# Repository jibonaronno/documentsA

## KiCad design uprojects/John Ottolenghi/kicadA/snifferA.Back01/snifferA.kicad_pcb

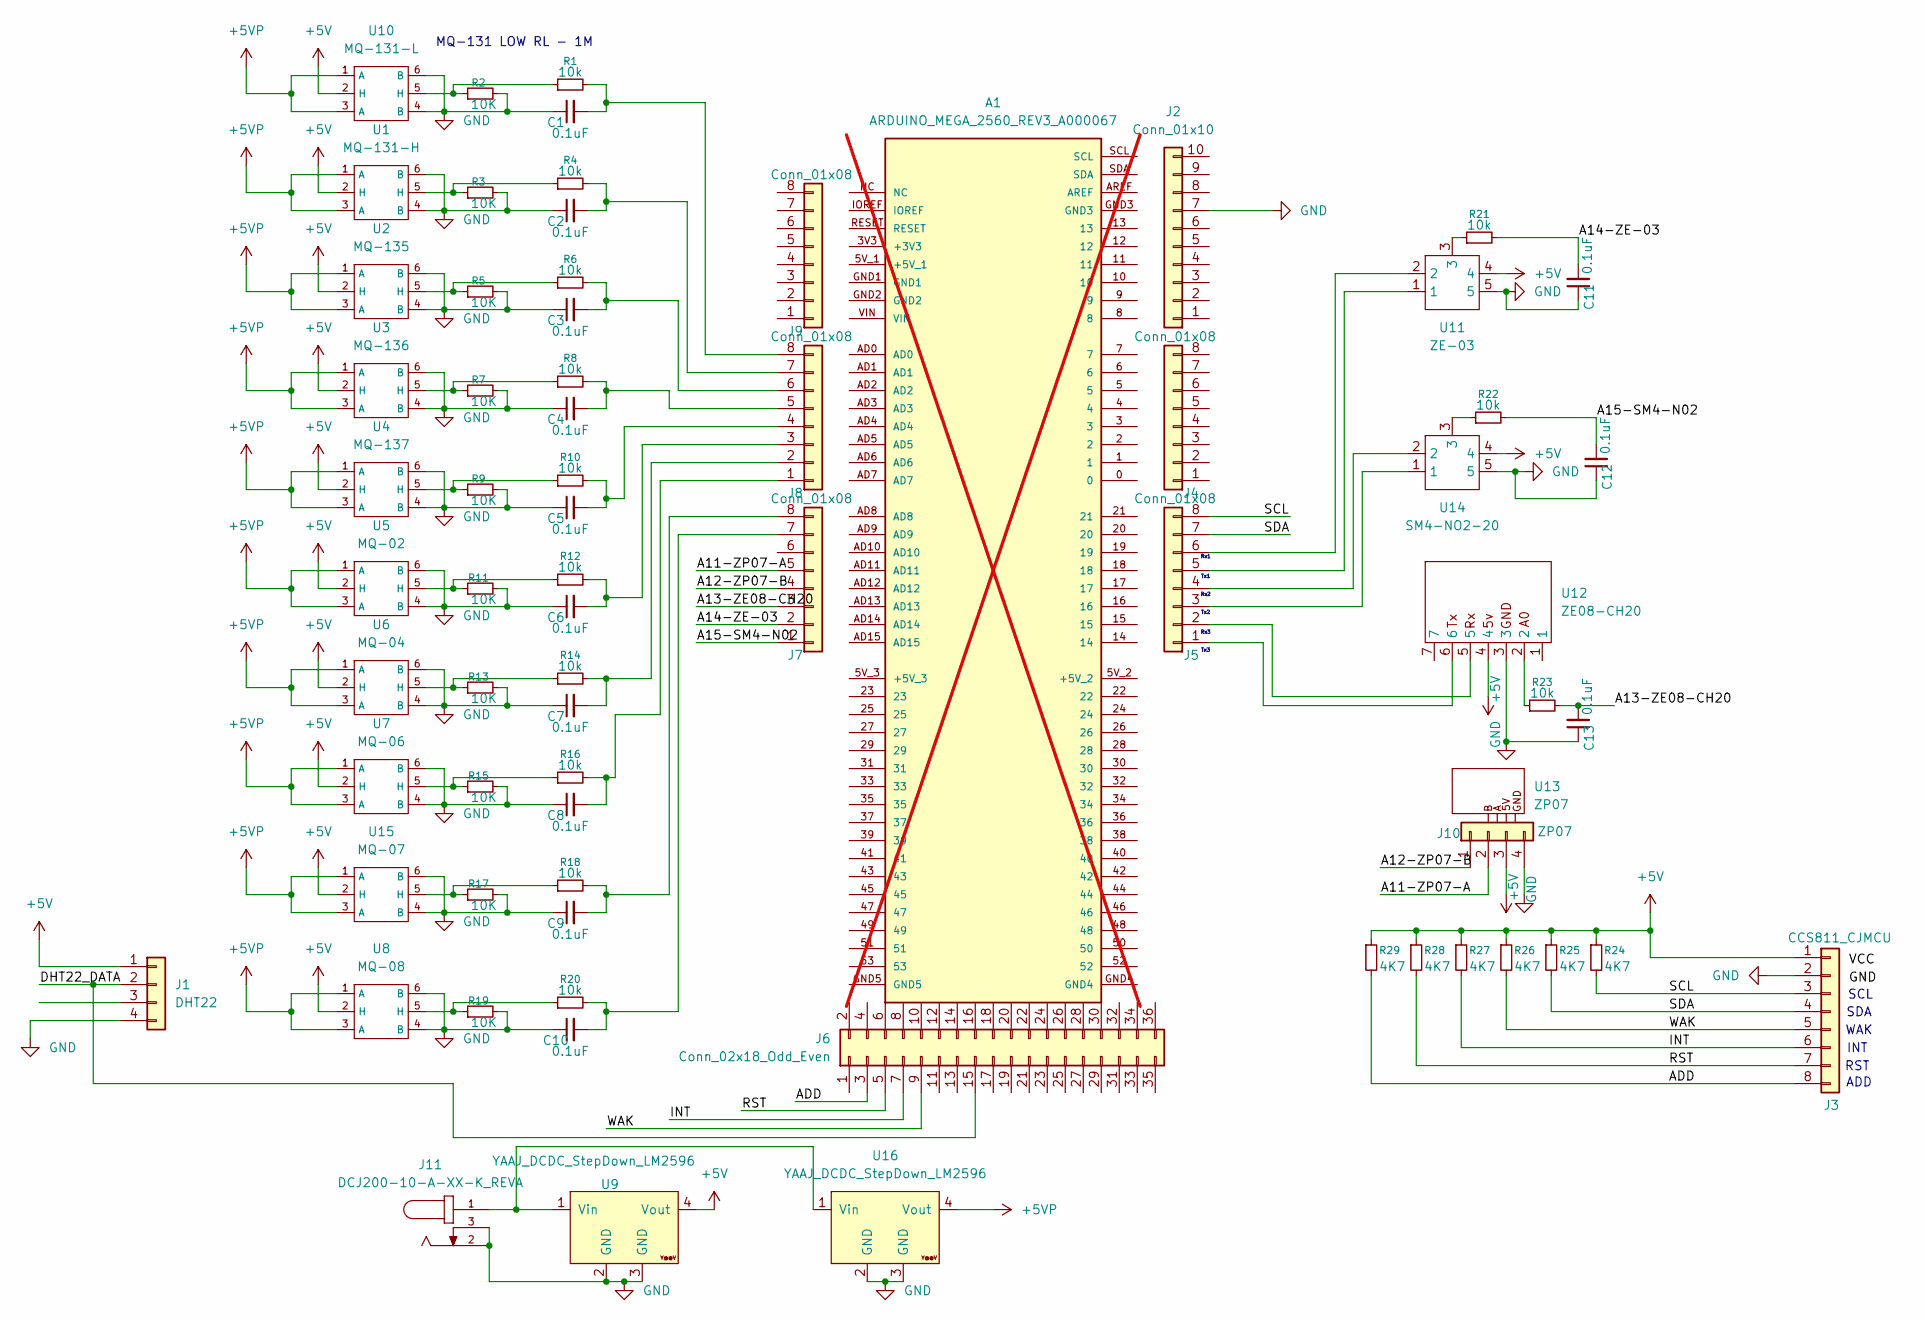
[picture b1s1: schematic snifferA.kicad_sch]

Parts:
A1: ARDUINO_MEGA_2560_REV3_A000067; ARDUINO_ARDUINO_MEGA_2560_REV3_A000067; PARTREV 3; not fitted
C1, C2, C3, C4, C5, C6, C7, C8, C9, C10, C11, C12, C13: 0.1uF; C_1206_3216Metric_Pad1.33x1.80mm_HandSolder; LCSC C24497
J1: DHT22; PinSocket_1x04_P2.54mm_Vertical
J2: Conn_01x10; PinHeader_1x10_P2.54mm_Vertical; LCSC C42431810
J3: CCS811_CJMCU; PinHeader_1x08_P2.54mm_Vertical; LCSC C6332201
J4, J5, J7, J8, J9: Conn_01x08; PinHeader_1x08_P2.54mm_Vertical; LCSC C6332201
J6: Conn_02x18_Odd_Even; PinHeader_2x18_P2.54mm_Vertical; LCSC C41376109
J10: ZP07; PinSocket_1x04_P2.54mm_Vertical
J11: DCJ200-10-A-XX-K_REVA; GCT_DCJ200-10-A-XX-K_REVA; PARTREV A
R1, R4, R6, R8, R10, R12, R14, R16, R18, R20, R21, R22, R23: 10k; R_1206_3216Metric; LCSC C2907370
R2, R3, R5, R7, R9, R11, R13, R15, R17, R19: 10K; R_1206_3216Metric; LCSC C2907370
R24, R25, R26, R27, R28, R29: 4K7; R_0603_1608Metric; LCSC C99782
U1: MQ-131-H; MQ
U2: MQ-135; MQ
U3: MQ-136; MQ
U4: MQ-137; MQ
U5: MQ-02; MQ
U6: MQ-04; MQ
U7: MQ-06; MQ
U8: MQ-08; MQ
U9, U16: YAAJ_DCDC_StepDown_LM2596
U10: MQ-131-L; MQ
U11: ZE-03; SM4-NO2-20
U12: ZE08-CH20; ZE-08
U13: ZP07; ZP07-FRAME
U14: SM4-NO2-20
U15: MQ-07; MQ

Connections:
+5V: J1.1, J3.1, J10.3, R24.1, R25.1, R26.1, R27.1, R28.1, R29.1, U1.2 (H), U2.2 (H), U3.2 (H), U4.2 (H), U5.2 (H), U6.2 (H), U7.2 (H), U8.2 (H), U9.4 (Vout), U10.2 (H), U11.4, U12.4, U14.4, U15.2 (H)
+5VP: U1.1 (A), U1.3 (A), U2.1 (A), U2.3 (A), U3.1 (A), U3.3 (A), U4.1 (A), U4.3 (A), U5.1 (A), U5.3 (A), U6.1 (A), U6.3 (A), U7.1 (A), U7.3 (A), U8.1 (A), U8.3 (A), U10.1 (A), U10.3 (A), U15.1 (A), U15.3 (A), U16.4 (Vout)
/A11-ZP07-A: J7.5, J10.2
/A12-ZP07-B: J7.4, J10.1
/A13-ZE08-CH20: C13.2, J7.3, R23.2
/A14-ZE-03: C11.2, J7.2, R21.2
/A15-SM4-N02: C12.2, J7.1, R22.2
/ADD: J3.8, J6.3, R29.2
/DHT22_DATA: J1.2, J6.15
/INT: J3.6, J6.7, R27.2
/RST: J3.7, J6.5, R28.2
/SCL: J3.3, J5.8, R24.2
/SDA: J3.4, J5.7, R25.2
/WAK: J3.5, J6.9, R26.2
GND: C1.1, C2.1, C3.1, C4.1, C5.1, C6.1, C7.1, C8.1, C9.1, C10.1, C11.1, C12.1, C13.1, J1.4, J2.7, J3.2, J10.4, J11.2, J11.3, R2.2, R3.2, R5.2, R7.2, R9.2, R11.2, R13.2, R15.2, R17.2, R19.2, U1.4 (B), U1.6 (B), U2.4 (B), U2.6 (B), U3.4 (B), U3.6 (B), U4.4 (B), U4.6 (B), U5.4 (B), U5.6 (B), U6.4 (B), U6.6 (B), U7.4 (B), U7.6 (B), U8.4 (B), U8.6 (B), U9.2 (GND), U9.3 (GND), U10.4 (B), U10.6 (B), U11.5, U12.3, U14.5, U15.4 (B), U15.6 (B), U16.2 (GND), U16.3 (GND)
unnamed: J5.1, U12.6
unnamed: J5.2, U12.5
unnamed: J5.3, U14.1
unnamed: J5.4, U14.2
unnamed: J5.5, U11.1
unnamed: J5.6, U11.2
unnamed: C10.2, J7.7, R20.2
unnamed: C9.2, J7.8, R18.2
unnamed: C8.2, J8.1, R16.2
unnamed: C7.2, J8.2, R14.2
unnamed: C6.2, J8.3, R12.2
unnamed: C5.2, J8.4, R10.2
unnamed: C4.2, J8.5, R8.2
unnamed: C3.2, J8.6, R6.2
unnamed: C2.2, J8.7, R4.2
unnamed: C1.2, J8.8, R1.2
unnamed: R1.1, R2.1, U10.5 (H)
unnamed: R3.1, R4.1, U1.5 (H)
unnamed: R5.1, R6.1, U2.5 (H)
unnamed: R7.1, R8.1, U3.5 (H)
unnamed: R9.1, R10.1, U4.5 (H)
unnamed: R11.1, R12.1, U5.5 (H)
unnamed: R13.1, R14.1, U6.5 (H)
unnamed: R15.1, R16.1, U7.5 (H)
unnamed: R17.1, R18.1, U15.5 (H)
unnamed: R19.1, R20.1, U8.5 (H)
unnamed: R21.1, U11.3
unnamed: R22.1, U14.3
unnamed: R23.1, U12.2
unnamed: J11.1, U9.1 (Vin), U16.1 (Vin)

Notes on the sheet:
Tx2
SCL
Tx1
Rx1
SDA
RST
Tx3
Rx3
WAK
Rx2
INT
MQ-131 LOW RL - 1M
ADD

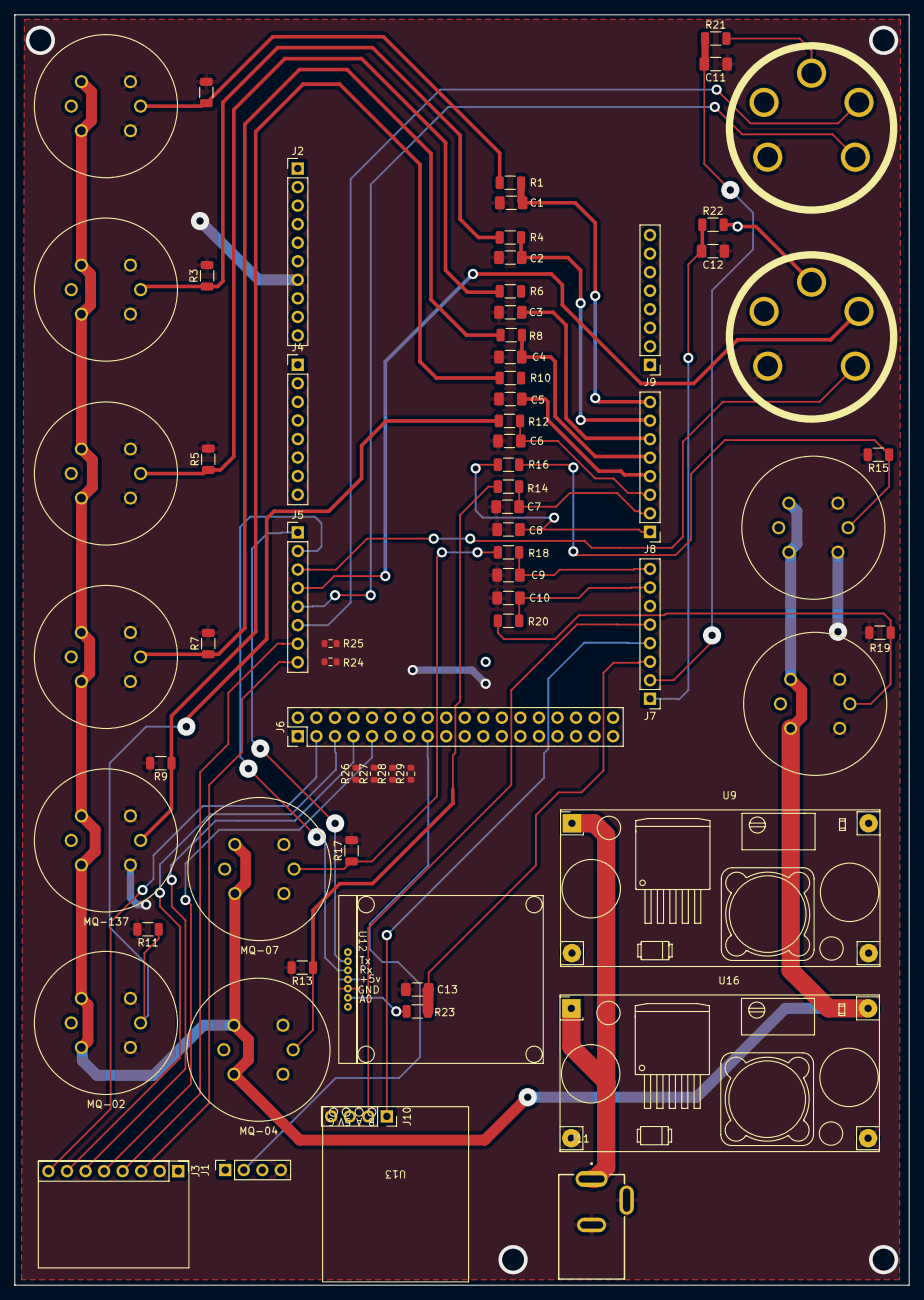
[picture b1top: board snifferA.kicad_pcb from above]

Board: 2 copper layers, 122.5 x 174.0 mm, 69 parts (0 on the bottom side), 45 nets.

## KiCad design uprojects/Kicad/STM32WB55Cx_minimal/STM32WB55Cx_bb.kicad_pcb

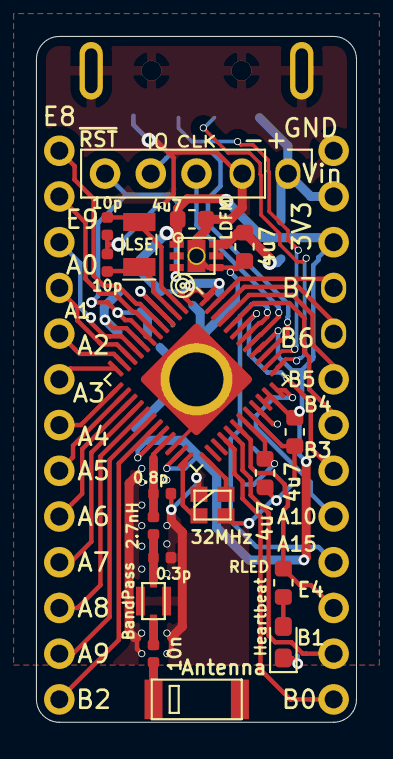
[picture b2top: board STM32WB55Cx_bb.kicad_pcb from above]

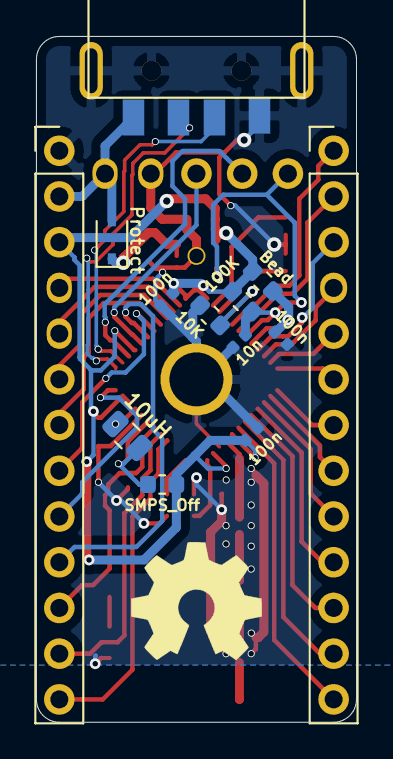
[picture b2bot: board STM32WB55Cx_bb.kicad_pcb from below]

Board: 2 copper layers, 17.8 x 38.1 mm, 32 parts (13 on the bottom side), 45 nets.

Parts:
AE1: Antenna; AA029_BLE-WiFi_Antenna
C1: 0.8p; C_0402_1005Metric
C2: 0.3p; C_0402_1005Metric
C3, C4, C5: 100n; C_0402_1005Metric
C6, C7, C10, C11: 4u7; C_0603_1608Metric
C8, C9: 10p; C_0402_1005Metric
C12, C13: 10n; C_0402_1005Metric
D1: Protect; D_SOD-323
D2: Heartbeat; LED_0603_1608Metric_Pad1.05x0.95mm_HandSolder
FL1: BandPass; LFB21x_SG_Bandpass
J1: Prog; PinHeader_1x05_P2.54mm_Vertical
J2: USB; USBA_Plug_Molex_480372200
J3: GPIO1; PinHeader_1x13_P2.54mm_Vertical
J4: GPIO2; PinHeader_1x13_P2.54mm_Vertical
JP1: SMPS_Off; R_0603_1608Metric
L1: 2.7nH; L_0402_1005Metric
L2: Bead; R_0603_1608Metric
L3: 10uH; L_0805_2012Metric
R1: 10K; R_0603_1608Metric
R2: 100K; R_0603_1608Metric
R3: RLED; R_0603_1608Metric
U1: STM32WB55Cx; QFN-48-1EP_7x7mm_P0.5mm_EP5.3x5.3mm
U2: LDFM; ST_LDFM_2x2DFN
Y1: LSE; Crystal_SMD_EuroQuartz_EQ161-2Pin_3.2x1.5mm
Y2: 32MHz; NX2016_XTal

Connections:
A0: J3.3, U1.9
A1: J3.4, U1.10
A2: J3.5, U1.11
A3: J3.6, U1.12
A4: J3.7, U1.13
A5: J3.8, U1.14
A6: J3.9, U1.15
A7: J3.10, U1.16
A8: J3.11, U1.17
A9: J3.12, U1.18
A10: J4.9, U1.36
A15: J4.10, U1.42
B0: J4.13, U1.28
B1: J4.12, U1.29
B2: J3.13, U1.19
B3: J4.8, U1.43
B4: J4.7, U1.44
B5: J4.6, U1.45
B6: J4.5, U1.46
B7: J4.4, U1.47
BOOT0: R1.2, U1.4
E4: J4.11, R3.1, U1.30
E8: J3.1, U1.5
E9: J3.2, U1.6
GND: C1.1, C2.1, C3.1, C4.1, C5.2, C6.1, C7.1, C8.2, C9.1, C10.1, C11.1, C13.2, D2.1, FL1.2, FL1.4, J1.2, J2.4, J2.5, J4.1, R1.1, U1.22, U1.32, U1.49, U2.4, U2.7, Y2.2
unnamed: AE1.1, C12.1
unnamed: C2.2, FL1.1, L1.2
unnamed: C3.2, L2.2, U1.8
unnamed: C7.2, JP1.1, L3.2, U1.31
unnamed: C8.1, U1.2, Y1.2
unnamed: C9.2, U1.3, Y1.1
unnamed: C12.2, FL1.3
unnamed: D2.2, R3.2
unnamed: L3.1, U1.33
unnamed: U1.24, Y2.1
unnamed: U1.25, Y2.3
RF1: C1.2, L1.1, U1.21
SWCLK: J1.3, U1.41
SWDIO: J1.4, U1.39
USB_D+: J2.3, U1.38
USB_D-: J2.2, U1.37
VAA: C11.2, D1.1, U2.5, U2.6
VDD: C4.2, C5.1, C6.2, C10.2, J4.3, JP1.2, L2.1, R2.1, U1.1, U1.20, U1.23, U1.34, U1.35, U1.40, U1.48, U2.1
VPP: D1.2, J1.1, J2.1, J4.2
~RST: C13.1, J1.5, R2.2, U1.7, U2.3

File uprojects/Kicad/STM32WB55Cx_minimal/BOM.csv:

Part ID,Part type,Part size,Part value,Example Digikey Item,Cost (qty: x),Comment
AE1,Antenna,Custom,Unictron H2U262GKBA0100,https://www.digikey.com/short/p2h8zn,$0.64,"Trace antennas are cheaper, but this seemed like a less failure-prone option for a first attempt."
C1,Capacitor,0402,0.8 pF,https://www.digikey.com/short/p2hrp7,$0.15,"50Ω matching filter capacitor. I used the values from ST's evaluation board, figuring they'd probably be fairly close. Ideal values will vary based on your board stackup. Prefer high-quality ceramic capacitors (C0G/NP0)"
C2,Capacitor,0402,0.3 pF,https://www.digikey.com/short/p2hrjw,$0.19,Another 50Ω matching filter capacitor.
"C3, C4, C5",Capacitor,0402,100 nF,https://www.digikey.com/short/p2hrz2,$0.30,Power supply decoupling capacitors. Prefer X5/X7 ceramic capacitors.
"C6, C7",Capacitor,0603,4.7 μF,https://www.digikey.com/short/p2hdqt,$0.34,SMPS decoupling capacitors for the built-in switching power supply. Prefer X5/X7 ceramic capacitors.
"C8, C9",Capacitor,0402,10 pF,https://www.digikey.com/short/p2hrhj,$0.20,Filtering capacitors for the 32.768KHz 'Low-Speed External' crystal oscillator. Prefer high-quality C0G/NP0 ceramic capacitors.
"C10, C11",Capacitor,0603,4.7 μF,https://www.digikey.com/short/p2hdqt,$0.34,Decoupling capacitors for the 3.3V voltage regulator. Prefer X5/X7 ceramic capacitors.
C12,Capacitor,0402,10 nF,https://www.digikey.com/short/p2hr54,$0.10,Filtering capacitor that sits between the 2.45GHz bandpass filter and the antenna. Prefer X7 ceramic capacitor.
C13,Capacitor,0402,10 nF,https://www.digikey.com/short/p2hr54,$0.10,Decoupling capacitor for the reset line.
D1,Schottky Diode,SOD-323,"20-40V, 0.5-2A",https://www.digikey.com/short/p2hd37,$0.31,Schottky diode to protect against reverse polarity.
D2,LED,0603,Your favorite color,https://www.digikey.com/short/p2hdpf,$0.14,LED indicator connected to pin E4.
FL1,Filter,0805,2.45GHz bandpass,https://www.digikey.com/short/p2hndq,$0.24,Bandpass filter which goes between the 50Ω impedance matching network and the antenna.
J1,Pins or Sockets,"0.1""",1x5,https://www.digikey.com/short/p2hd9v,$0.17,"Programming header; reset, SWDIO, SWCLK, ground, power input. These pin headers are commodities, and it's much chepaer to order them in bulk 1x40 rows."
J2,USB A Plug,-,-,https://www.digikey.com/short/p2hn02,$1.30,"USB-A plug, since the chip has a USB peripheral."
"J3, J4",Pins or Sockets,"0.1""",1x13,https://www.digikey.com/short/p2hdhn,$0.64,"GPIO pin headers, for plugging into a breadboard or socket."
JP1,Jumper,0603,0Ω,https://www.digikey.com/short/p2hdnn,$0.10,Fit a jumper here to disable the internal switching power supply. Requires a corresponding firmware configuration.
L1,Inductor,0402,2.7 nH,https://www.digikey.com/short/p2hn1q,$0.10,"50Ω matching filter inductor. Again, the value is from ST's reference design."
L2,Ferrite Bead,0603,-,https://www.digikey.com/short/p2h080,$0.10,A ferrite bead to filter out high-frequency noise on the analog voltage pin.
L3,Inductor,0805,10 μH,https://www.digikey.com/short/p2h03f,$0.14,Inductor for the internal switching power supply.
R1,Resistor,0603,10 KΩ,https://www.digikey.com/short/p2hddd,$0.10,Pull-down resistor for the 'BOOT0' pin.
R2,Resistor,0603,100 KΩ,https://www.digikey.com/short/p2hd0t,$0.10,"Pull-up resistor for the reset pin. This probably isn't needed since the chips have an internal ~47KΩ pull-up on this pin, but the reference design has a pull-up so I included one."
R3,Resistor,0603,~1 KΩ,https://www.digikey.com/short/p2hdw9,$0.10,Resistor for the LED indicator. Adjust depending on how bright or dim you want the LED to be.
U1,Microcontroller,QFN-48,STM32WB55Cx,https://www.digikey.com/short/p2hd4t,$6.65,Core microcontroller; available with either 512KB or 1MB of Flash memory.
U2,Voltage Regulator,DFN-6,LFDM33PVR,https://www.digikey.com/short/p2hdm4,$0.75,500mA low-dropout linear voltage regulator.
Y1,Crystal,3.2x1.5mm,32.768KHz,https://www.digikey.com/short/p2h0zh,$0.41,Low-Speed External' crystal oscillator.
Y2,Crystal,2.0x1.6mm,32MHz,https://www.digikey.com/short/p2hdhc,$0.64,High-Speed External' crystal oscillator.
Total:,-,-,-,-,$14.35,-

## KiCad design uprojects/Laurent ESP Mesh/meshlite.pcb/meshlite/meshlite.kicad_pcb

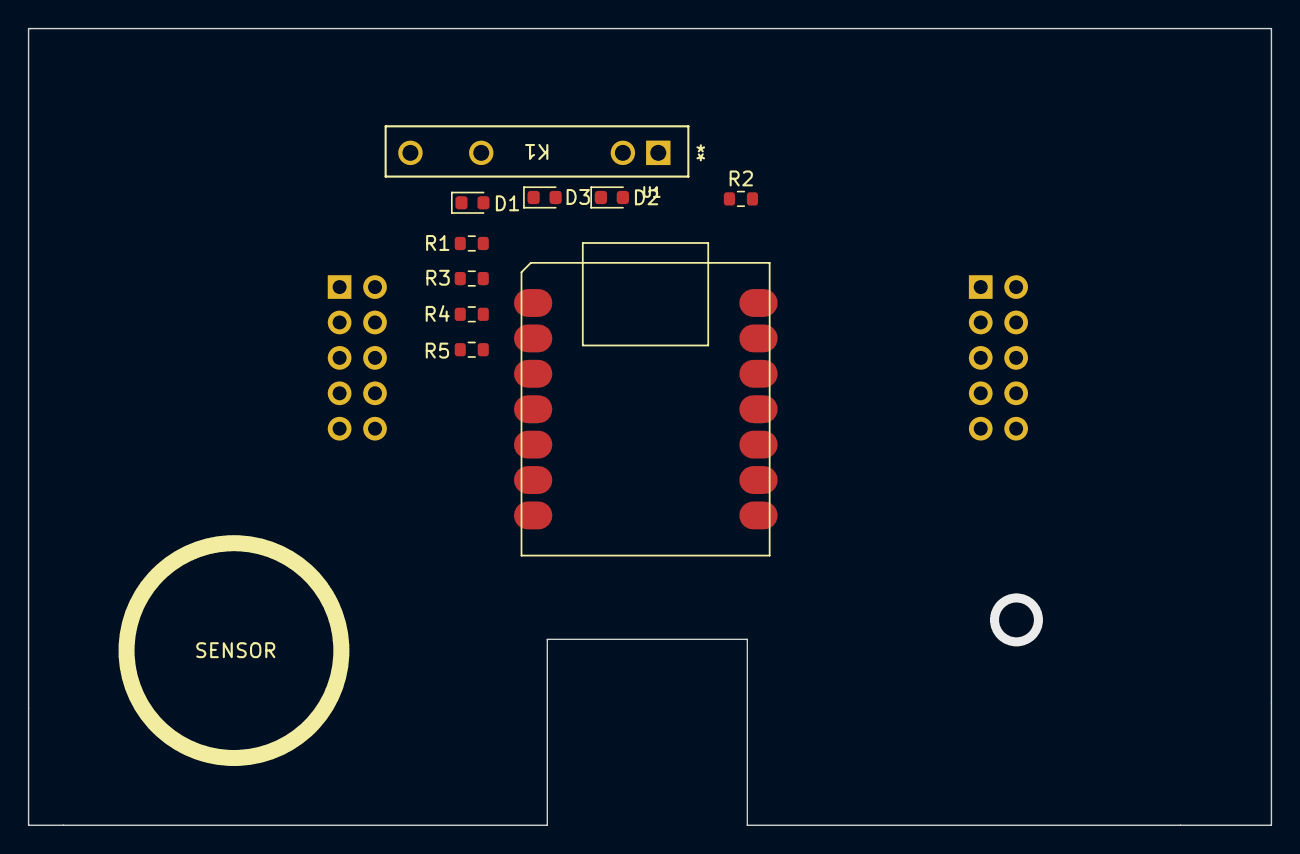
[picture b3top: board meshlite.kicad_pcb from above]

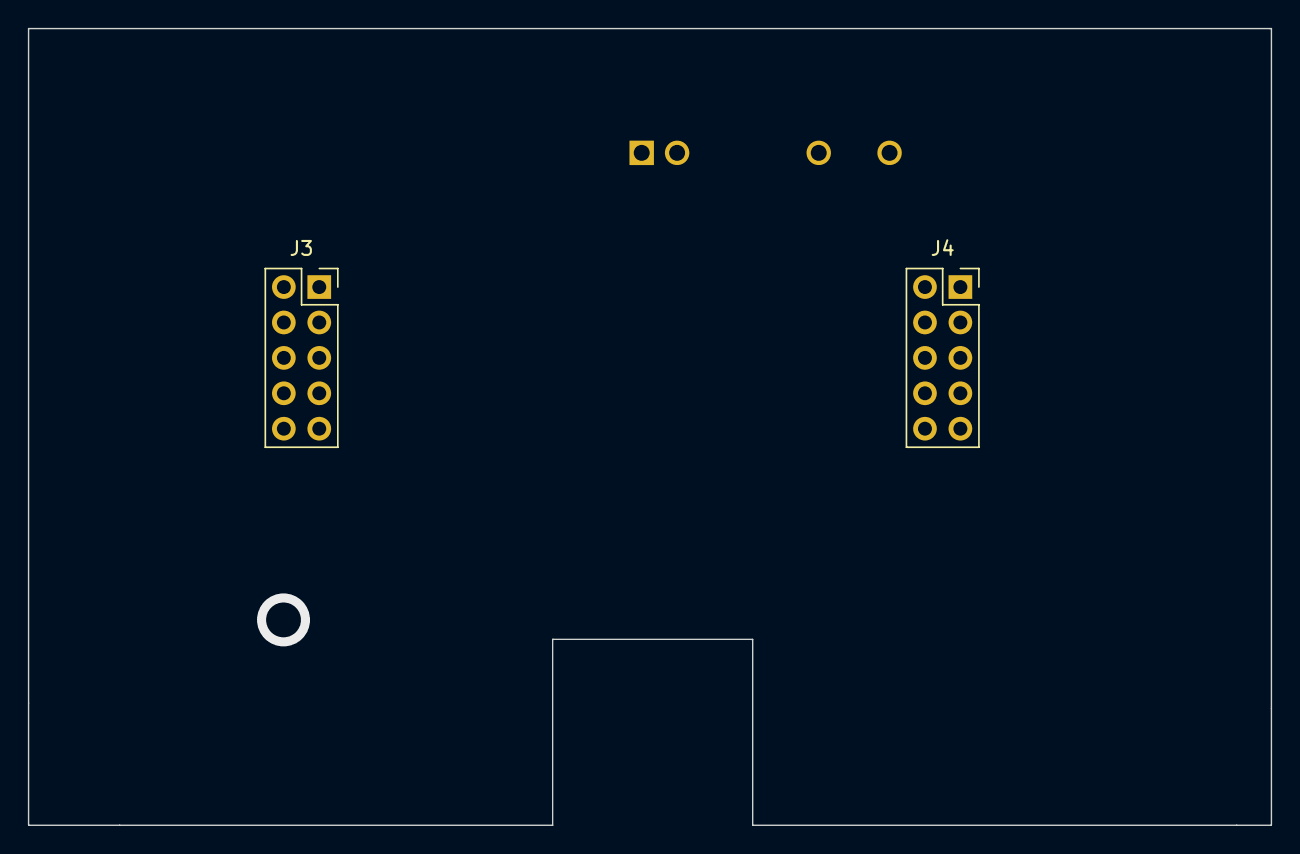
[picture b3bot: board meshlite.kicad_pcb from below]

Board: 2 copper layers, 89.2 x 57.1 mm, 12 parts (2 on the bottom side), 10 nets, no tracks yet.

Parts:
D1, D2, D3: LED; LED_0603_1608Metric
J3, J4: Conn_02x05_Odd_Even; PinSocket_2x05_P2.54mm_Vertical
K1: CPC1916Y
R1, R2: R_Small; R_0603_1608Metric
R3, R4, R5: 470E; R_0603_1608Metric
U1: MOUDLE-SEEEDUINO-XIAO-ESP32C3; MOUDLE14P-SMD-2.54-21X17.8MM

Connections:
A0: R1.2, U1.1 (PA02_A0_D0)
GND: D1.1 (K), D2.1 (K), D3.1 (K), K1.2
unnamed: D1.2 (A), R3.1
unnamed: D2.2 (A), R4.1
unnamed: D3.2 (A), R5.1
unnamed: K1.1, R2.2
unnamed: R3.2, U1.2 (PA4_A1_D1)
unnamed: R2.1, U1.11 (PA6_A10_D10_MOSI)
unnamed: R4.2, U1.3 (PA10_A2_D2)
unnamed: R5.2, U1.4 (PA11_A3_D3)

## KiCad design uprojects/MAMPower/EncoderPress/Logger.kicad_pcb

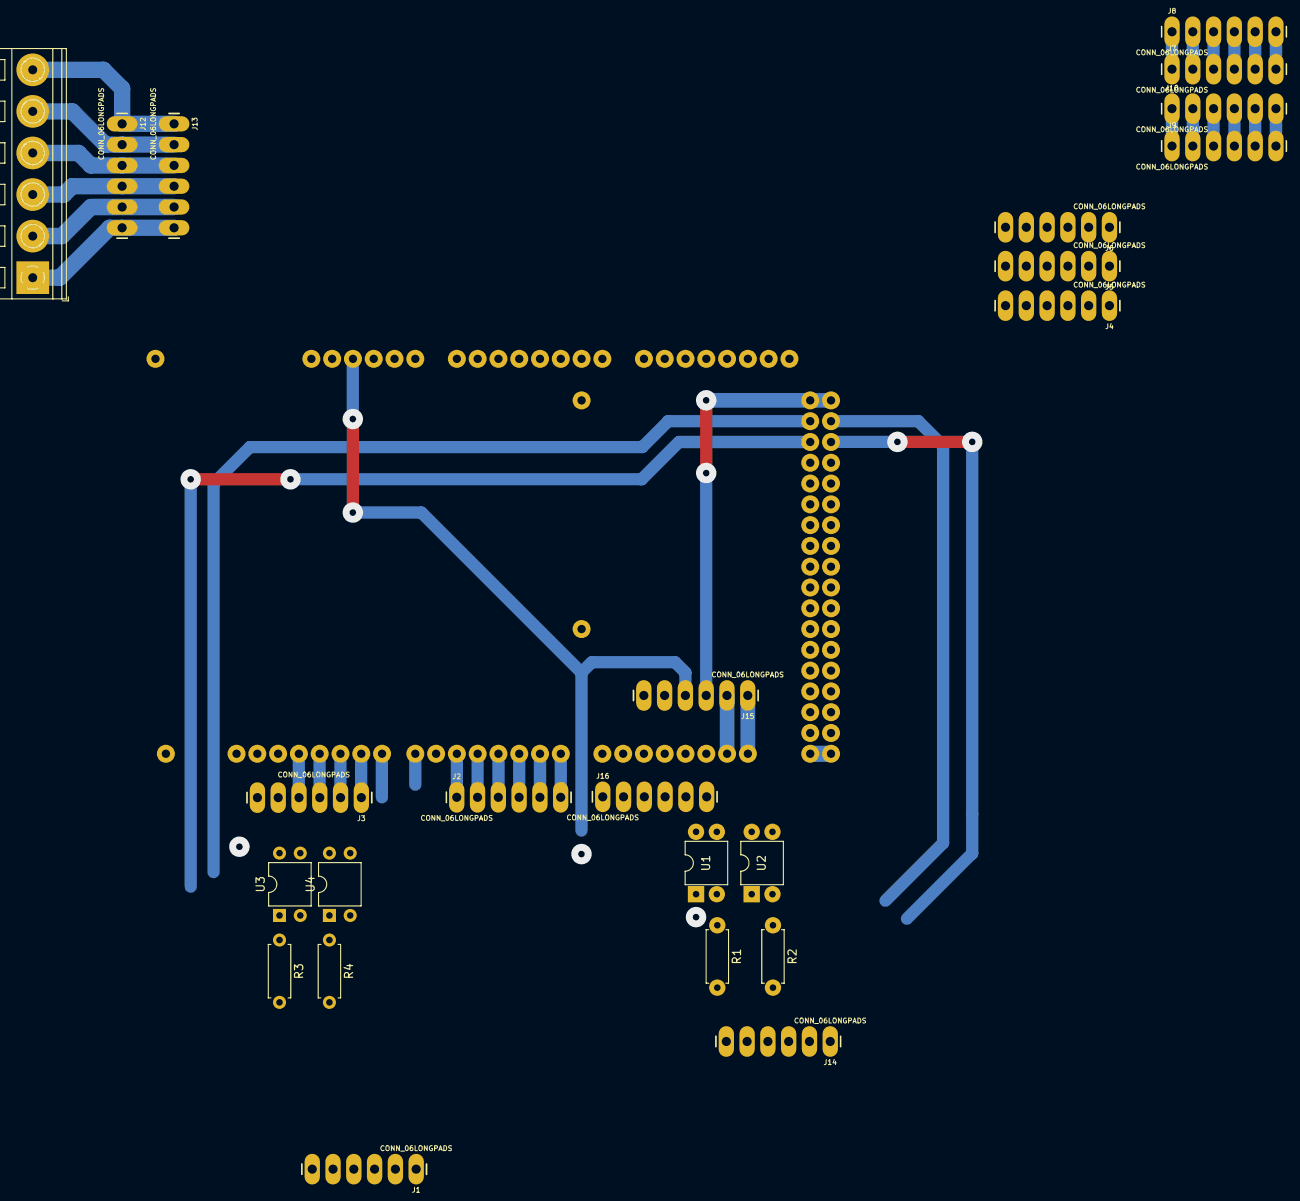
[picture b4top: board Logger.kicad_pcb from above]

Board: 2 copper layers, 25 parts (1 on the bottom side), 53 nets.

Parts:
B1: ARDUINO_MEGA_R3FULL-SparkFun-Boards; ARDUINO_MEGA
J1, J2, J3, J4, J5, J6, J7, J8, J9, J10, J12, J13, J14, J15, J16: CONN_06LONGPADS; 1X06_LONGPADS
J11: Screw_Terminal_01x06; TerminalBlock_RND_205-00236_1x06_P5.08mm_Horizontal
R1, R2, R3, R4: 330E; R_Axial_DIN0207_L6.3mm_D2.5mm_P7.62mm_Horizontal
U1, U2, U3, U4: PC817; DIP-4_W7.62mm

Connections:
13: B1.13, J3.5
GND: B1.GND@, J3.6, J4.3, J4.4, J5.3, J5.4, J6.3, J6.4, J15.3, U1.3, U2.3
unnamed: B1.0, J2.6
unnamed: B1.1, J2.5
unnamed: B1.2, J2.4
unnamed: B1.3, J2.3
unnamed: B1.4, J2.2
unnamed: B1.5, J2.1
unnamed: B1.9, J3.1
unnamed: B1.10, J3.2
unnamed: B1.11, J3.3
unnamed: B1.12, J3.4
unnamed: B1.14, J16.1
unnamed: B1.15, J16.2
unnamed: B1.16, J16.3
unnamed: B1.17, J16.4
unnamed: B1.18, J16.5
unnamed: B1.19, J16.6
unnamed: J1.1, U4.2
unnamed: J1.2, R4.2
unnamed: J1.3, U3.2
unnamed: J5.1, J6.1
unnamed: J5.2, J6.2
unnamed: J5.6, J6.6
unnamed: J7.1, J8.1
unnamed: J7.2, J8.2
unnamed: J7.3, J8.3
unnamed: J7.4, J8.4
unnamed: J7.5, J8.5
unnamed: J7.6, J8.6
unnamed: J9.1, J10.1
unnamed: J9.2, J10.2
unnamed: J9.3, J10.3
unnamed: J9.4, J10.4
unnamed: J9.5, J10.5
unnamed: J9.6, J10.6
unnamed: J11.1, J12.6, J13.6
unnamed: J11.2, J12.5, J13.5
unnamed: J11.3, J12.4, J13.4
unnamed: J11.4, J12.3, J13.3
unnamed: J11.5, J12.2, J13.2
unnamed: J11.6, J12.1, J13.1
unnamed: J14.1, U2.2
unnamed: J14.2, R2.2
unnamed: J14.3, U1.2
unnamed: J14.4, R1.2
unnamed: R1.1, U1.1
unnamed: R2.1, U2.1
unnamed: R3.1, U3.1
unnamed: R4.1, U4.1
SCL: B1.21, J15.1
SDA: B1.20, J15.2
VCC: B1.5V@0, B1.5V@1, B1.5V@2, J4.5, J5.5, J6.5, J15.4
